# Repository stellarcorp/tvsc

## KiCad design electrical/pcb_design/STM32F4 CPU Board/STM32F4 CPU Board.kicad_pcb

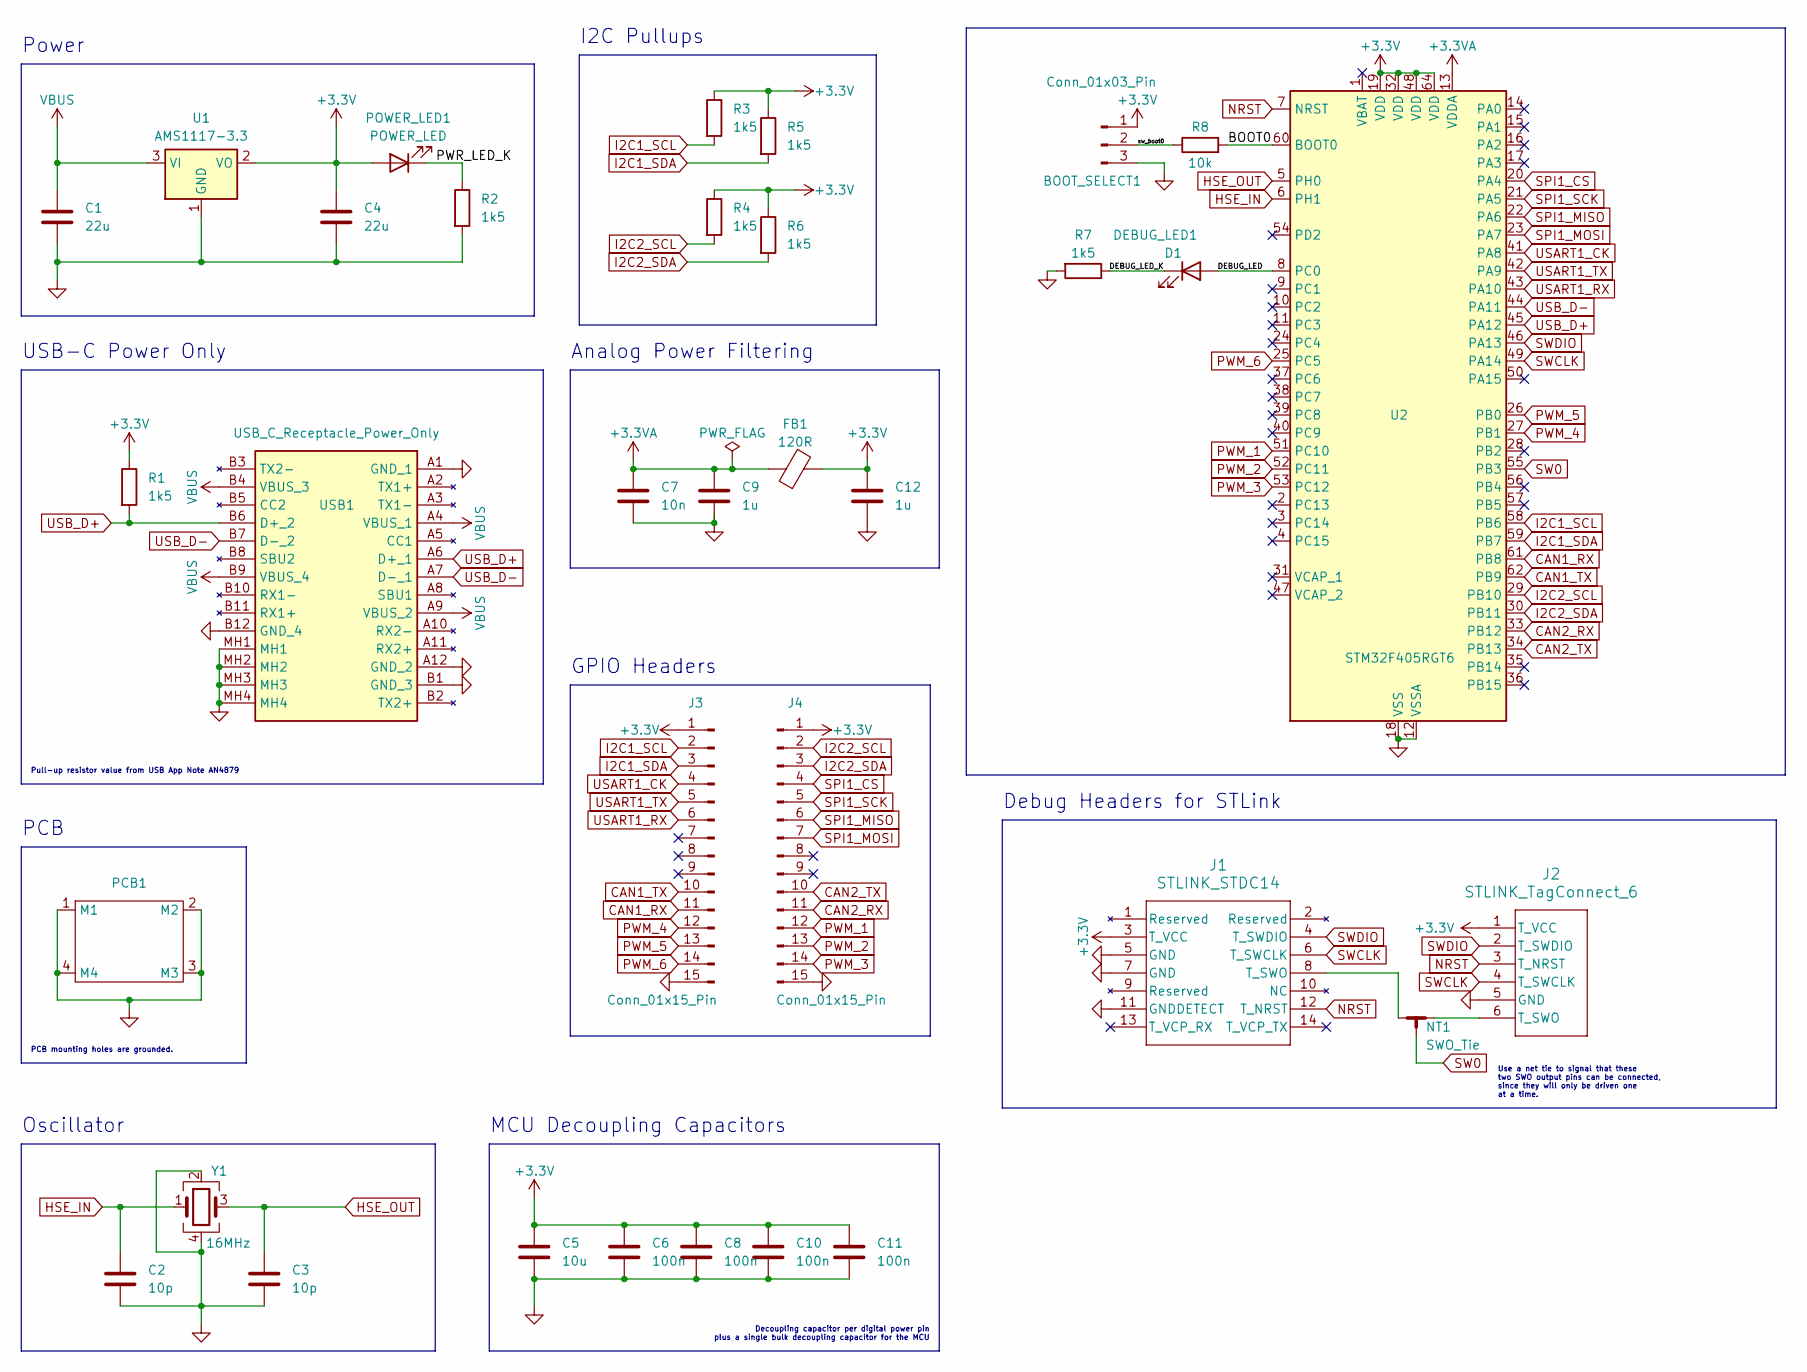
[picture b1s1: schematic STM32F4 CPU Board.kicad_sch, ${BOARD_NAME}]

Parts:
BOOT_SELECT1: Conn_01x03_Pin; PinHeader_1x03_P2.54mm_Vertical
C1, C4: 22u; C_0805_2012Metric; MPN C45783
C2, C3: 10p; C_0402_1005Metric; MPN C32949
C5: 10u; C_0603_1608Metric; MPN C19702
C6, C8, C10, C11: 100n; C_0402_1005Metric; MPN C1525
C7: 10n; C_0402_1005Metric; MPN C15195
C9, C12: 1u; C_0603_1608Metric; MPN C15849
D1: DEBUG_LED1; LED_0603_1608Metric; MPN C72041
FB1: 120R; L_0603_1608Metric; MPN C22787
J1: STLINK_STDC14; PinHeader_2x07_P1.27mm_Vertical; MPN C2881789
J2: STLINK_TagConnect_6; Tag-Connect_TC2030-IDC-NL_2x03_P1.27mm_Vertical
J3, J4: Conn_01x15_Pin; PinSocket_1x15_P2.54mm_Vertical; MPN C2883481
NT1: SWO_Tie; NetTie-3_SMD_Pad0.5mm
PCB1: Standard_PCB_Shape
POWER_LED1: POWER_LED; LED_0603_1608Metric; MPN C72043
R1, R2, R3, R4, R5, R6, R7: 1k5; R_0402_1005Metric; MPN C25867
R8: 10k; R_0402_1005Metric; MPN C25744
U1: AMS1117-3.3; SOT-223-3_TabPin2; MPN C6186
U2: STM32F405RGT6; LQFP-64_10x10mm_P0.5mm
USB1: USB_C_Receptacle_Power_Only; 12401832E402A; MPN C464604
Y1: 16MHz; Crystal_SMD_3225-4Pin_3.2x2.5mm; MPN C2857621

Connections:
+3.3V: BOOT_SELECT1.1, C4.1, C5.1, C6.1, C8.1, C10.1, C11.1, C12.1, FB1.2, J1.3 (T_VCC), J2.1 (T_VCC), J3.1, J4.1, POWER_LED1.2 (A), R1.1, R3.1, R4.1, R5.1, R6.1, U1.2 (VO), U2.19 (VDD), U2.32 (VDD), U2.48 (VDD), U2.64 (VDD)
+3.3VA: C7.1, C9.1, FB1.1, U2.13 (VDDA)
/BOOT0: R8.2, U2.60 (BOOT0)
/DEBUG_LED: D1.2 (A), U2.8 (PC0)
/DEBUG_LED_K: D1.1 (K), R7.1
/PWR_LED_K: POWER_LED1.1 (K), R2.1
/sw_boot0: BOOT_SELECT1.2, R8.1
CAN1_RX: J3.11, U2.61 (PB8)
CAN1_TX: J3.10, U2.62 (PB9)
CAN2_RX: J4.11, U2.33 (PB12)
CAN2_TX: J4.10, U2.34 (PB13)
GND: BOOT_SELECT1.3, C1.2, C2.2, C3.2, C4.2, C5.2, C6.2, C7.2, C8.2, C9.2, C10.2, C11.2, C12.2, J1.5 (GND), J1.7 (GND), J1.11 (GNDDETECT), J2.5 (GND), J3.15, J4.15, PCB1.1 (M1), PCB1.2 (M2), PCB1.3 (M3), PCB1.4 (M4), R2.2, R7.2, U1.1 (GND), U2.12 (VSSA), U2.18 (VSS), U2.63 (VSS), USB1.A1 (GND_1), USB1.A12 (GND_2), USB1.B1 (GND_3), USB1.B12 (GND_4), USB1.MH1, USB1.MH2, USB1.MH3, USB1.MH4, Y1.2, Y1.4
HSE_IN: C2.1, U2.6 (PH1), Y1.1
HSE_OUT: C3.1, U2.5 (PH0), Y1.3
I2C1_SCL: J3.2, R3.2, U2.58 (PB6)
I2C1_SDA: J3.3, R5.2, U2.59 (PB7)
I2C2_SCL: J4.2, R4.2, U2.29 (PB10)
I2C2_SDA: J4.3, R6.2, U2.30 (PB11)
NRST: J1.12 (T_NRST), J2.3 (T_NRST), U2.7 (NRST)
unnamed: J1.8 (T_SWO), NT1.1
unnamed: J2.6 (T_SWO), NT1.2
PWM_1: J4.12, U2.51 (PC10)
PWM_2: J4.13, U2.52 (PC11)
PWM_3: J4.14, U2.53 (PC12)
PWM_4: J3.12, U2.27 (PB1)
PWM_5: J3.13, U2.26 (PB0)
PWM_6: J3.14, U2.25 (PC5)
SPI1_CS: J4.4, U2.20 (PA4)
SPI1_MISO: J4.6, U2.22 (PA6)
SPI1_MOSI: J4.7, U2.23 (PA7)
SPI1_SCK: J4.5, U2.21 (PA5)
SW0: NT1.3, U2.55 (PB3)
SWCLK: J1.6 (T_SWCLK), J2.4 (T_SWCLK), U2.49 (PA14)
SWDIO: J1.4 (T_SWDIO), J2.2 (T_SWDIO), U2.46 (PA13)
USART1_CK: J3.4, U2.41 (PA8)
USART1_RX: J3.6, U2.43 (PA10)
USART1_TX: J3.5, U2.42 (PA9)
USB_D+: R1.2, U2.45 (PA12), USB1.A6 (D+_1), USB1.B6 (D+_2)
USB_D-: U2.44 (PA11), USB1.A7 (D-_1), USB1.B7 (D-_2)
VBUS: C1.1, U1.3 (VI), USB1.A4 (VBUS_1), USB1.A9 (VBUS_2), USB1.B4 (VBUS_3), USB1.B9 (VBUS_4)

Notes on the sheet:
Use a net tie to signal that these two SWO output pins can be connected, since they will only be driven one at a time.
GPIO Headers
Decoupling capacitor per digital power pin plus a single bulk decoupling capacitor for the MCU
I2C Pullups
PCB mounting holes are grounded.
PCB
Debug Headers for STLink
Power
Pull-up resistor value from USB App Note AN4879
MCU Decoupling Capacitors
Analog Power Filtering
Oscillator
USB-C Power Only

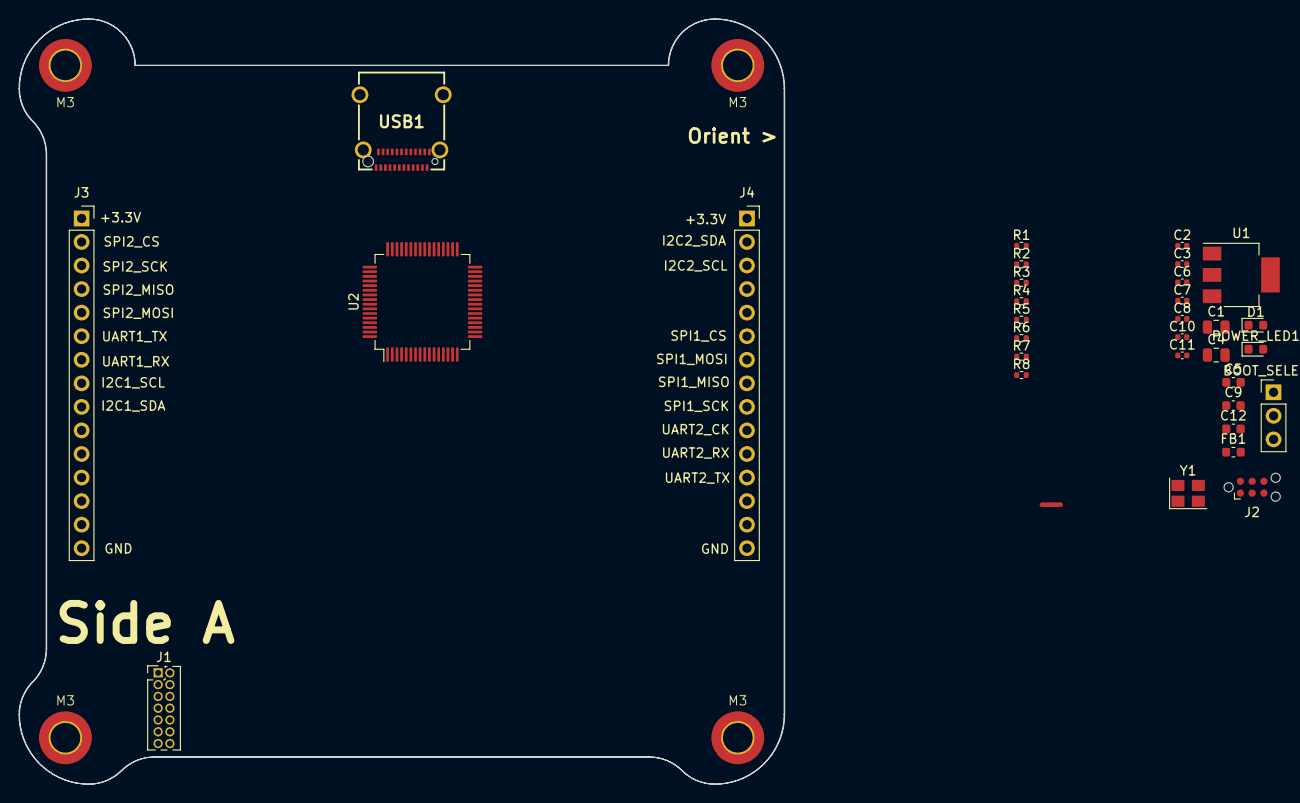
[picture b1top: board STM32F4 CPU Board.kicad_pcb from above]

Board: 2 copper layers, 82.5 x 82.5 mm, 34 parts (0 on the bottom side), 40 nets.

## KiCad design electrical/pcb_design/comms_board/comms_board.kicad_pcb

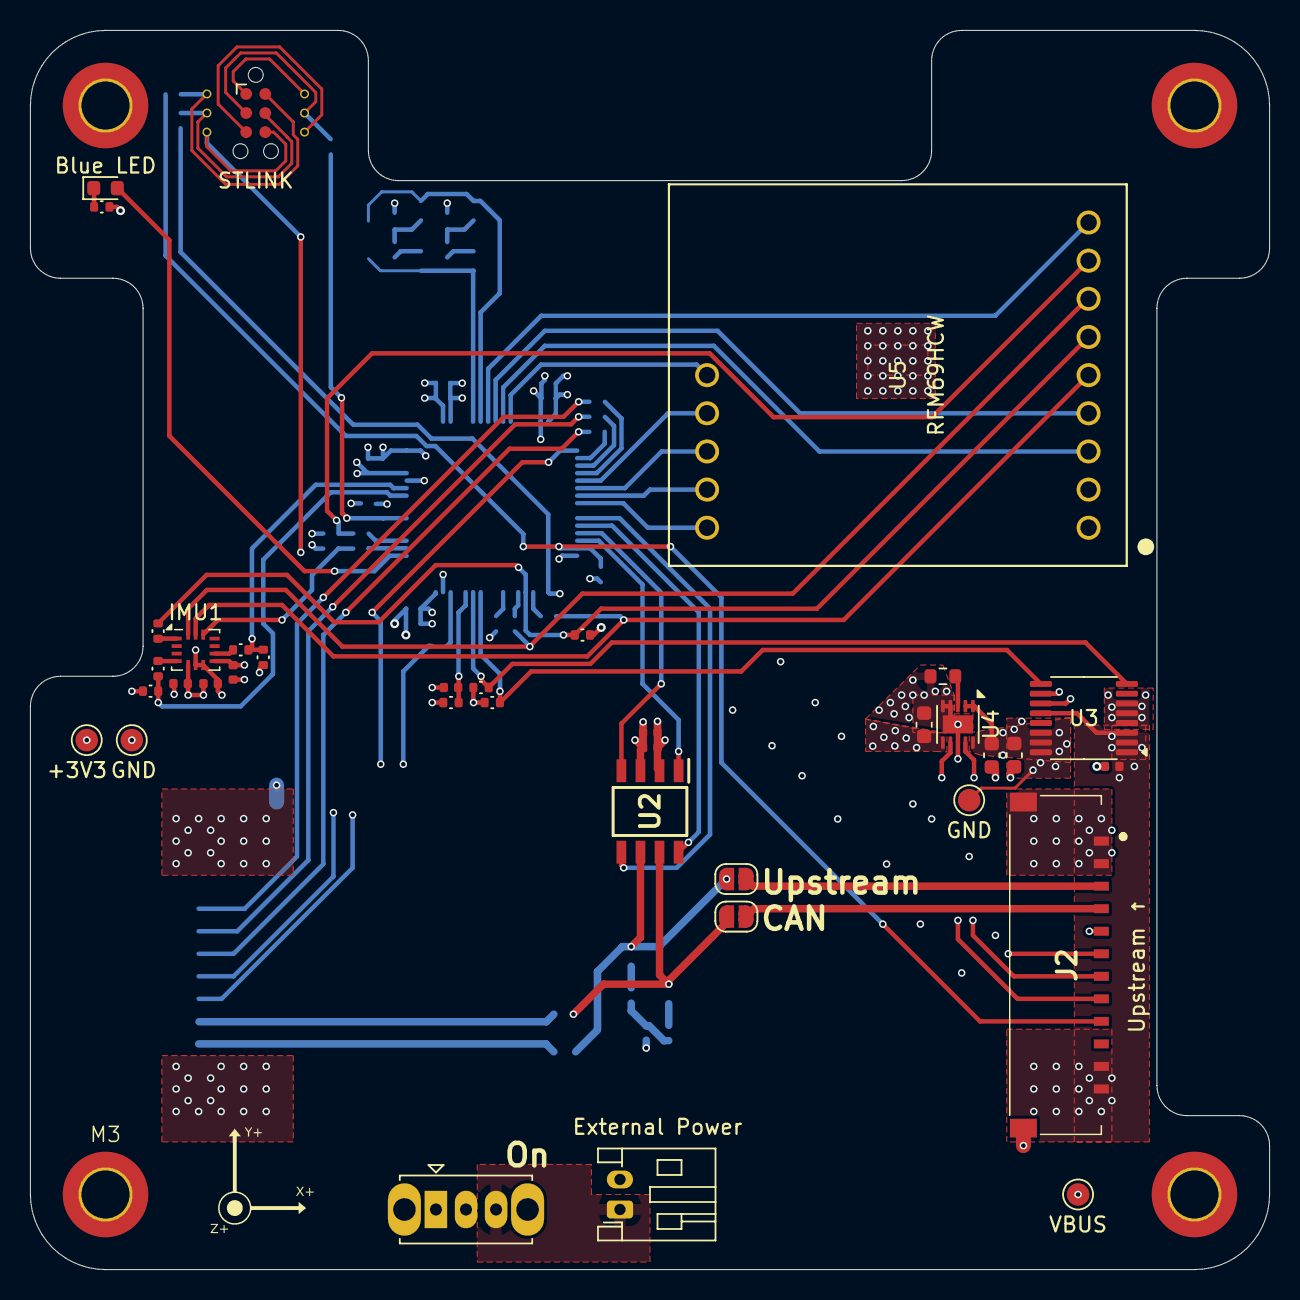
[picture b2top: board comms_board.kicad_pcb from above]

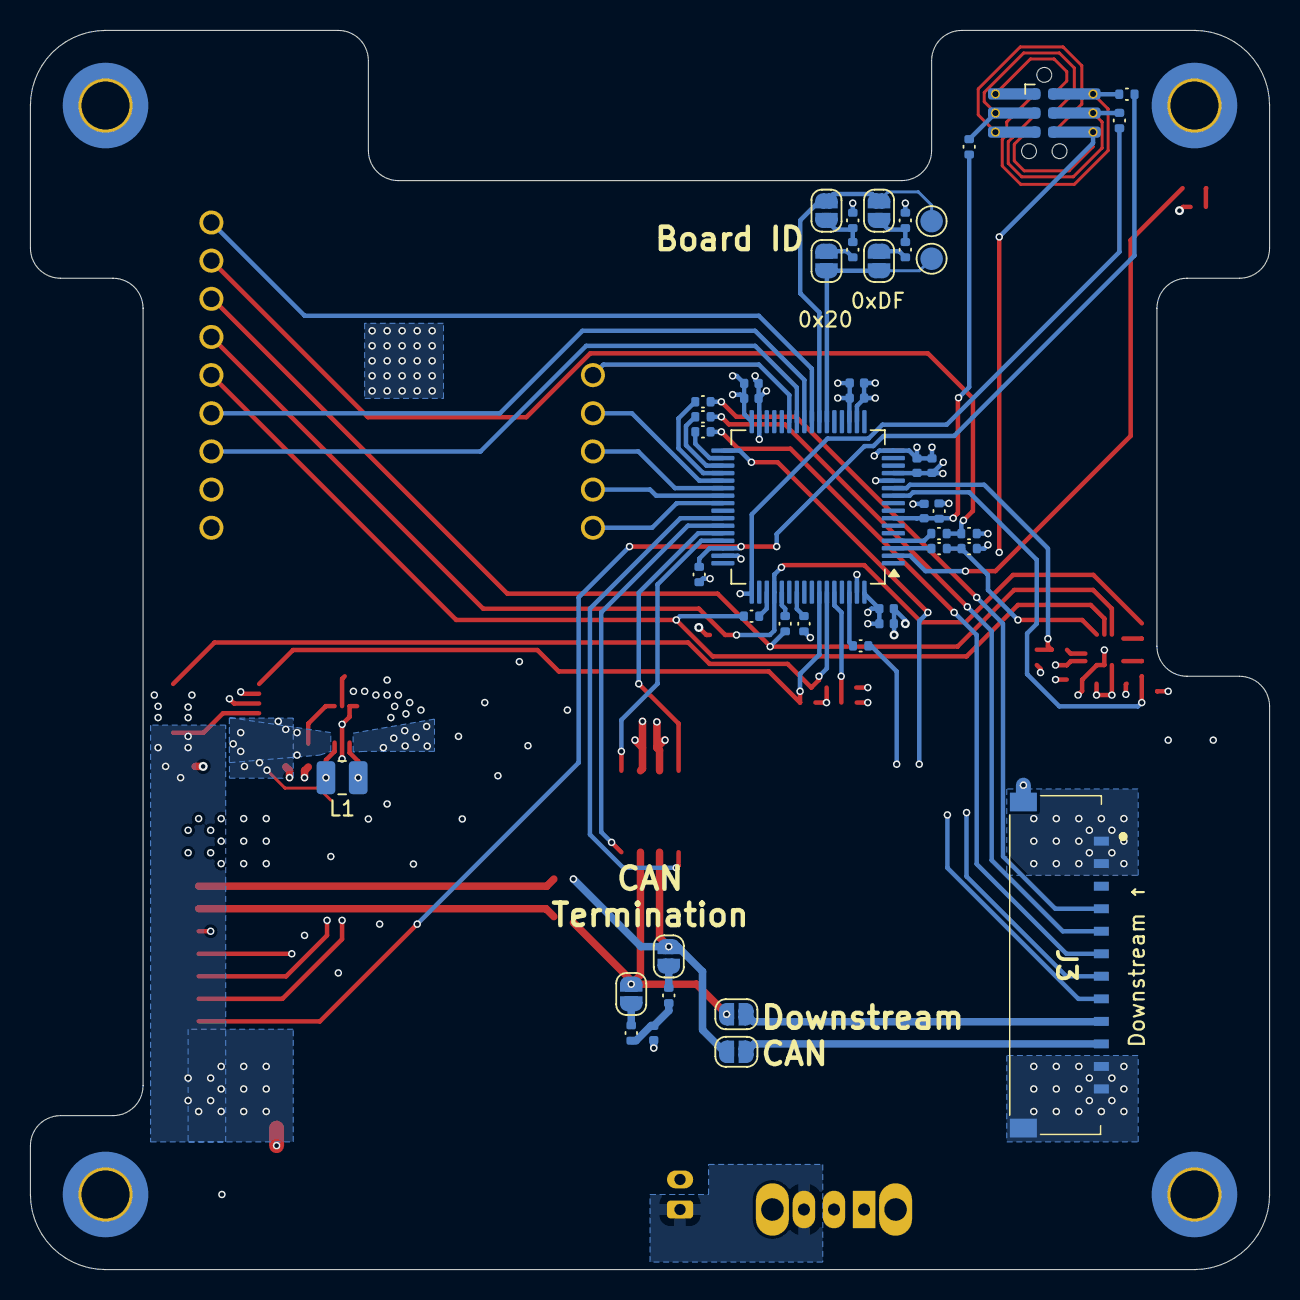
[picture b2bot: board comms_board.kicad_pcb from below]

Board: 4 copper layers, 82.5 x 82.5 mm, 83 parts (46 on the bottom side), 71 nets.

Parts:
C1, C2, C3, C7, C8, C9, C13, C14, C19, C20: 100n; Nondescript_C_0402_1005Metric
C4: 10u; Nondescript_C_0402_1005Metric
C5, C17: 22u; Nondescript_C_0603_1608Metric
C6: 10u; Nondescript_C_0603_1608Metric
C10, C11, C12, C15, C16, C18: 1u; Nondescript_C_0402_1005Metric
D1: Blue LED; LED_0603_1608Metric
J1: STLINK; Double-Sided_Tag-Connect_TC2030-IDC-NL_2x03_P1.27mm_Vertical
J2: Molex_504050-1291; Bus Connector (Target)
J3: Molex_504050-1291; Bus Connector (Control)
J4: External Power; JST_PH_S2B-PH-K_1x02_P2.00mm_Horizontal
JP1, JP2, JP3, JP4, JP5, JP6: SolderJumper_2_Open; SolderJumper-2_P1.3mm_Open_RoundedPad1.0x1.5mm
JP7, JP9: 0xDF; SolderJumper-2_P1.3mm_Open_RoundedPad1.0x1.5mm
JP8, JP10: 0x20; SolderJumper-2_P1.3mm_Open_RoundedPad1.0x1.5mm
L1: 2.2µH; L_1008_2520Metric
PCB1: Core_Board_Shape_Space_Invader_2
R1, R3, R6, R11, R12, R17, R25, R26, R33, R48: 9k31; Nondescript_R_0402_1005Metric
R2, R4, R5, R7, R8, R9, R18, R19, R20, R21, R22, R23, R34, R37, R38, R39: 33; Nondescript_R_0402_1005Metric
R10: 36k5; Nondescript_R_0603_1608Metric
R13, R16: 3k16; Nondescript_R_0402_1005Metric
R14, R15: 221k; Nondescript_R_0402_1005Metric
R49, R50: 60; Nondescript_R_0402_1005Metric
SW1: SW_SPDT; SW_Slide_SPDT_Straight_CK_OS102011MS2Q
TP1: VBUS; TestPoint_Pad_D1.5mm
TP2, TP3: GND; TestPoint_Pad_D1.5mm
TP4: +3V3; TestPoint_Pad_D1.5mm
TP5: BOARD_ID_SENSE; TestPoint_Pad_D1.5mm
TP6: BOARD_ID_POWER; TestPoint_Pad_D1.5mm
U1: STM32L452RCTx; LQFP-64_10x10mm_P0.5mm
U2: TCAN330DR; SOIC127P600X175-8N
U3: INA260; TSSOP-16_4.4x5mm_P0.65mm
U4: TPS63900; WSON-10-1EP_2.5x2.5mm_P0.5mm_EP1.2x2mm
U5: RFM69HCW; RFM69HCW_Adafruit_Breakout
U6: IMU1; Bosch_LGA-14_3x2.5mm_P0.5mm

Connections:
+3V3: C5.1, C7.1, C8.1, C9.1, C10.1, C11.1, C12.1, C13.1, C14.1, C15.1, C16.1, C18.1, C19.1, C20.1, J1.1 (T_VCC), R1.1, R6.1, R11.1, R12.1, R17.1, R25.1, R26.1, R33.1, R48.1, TP4.1, U1.13 (VDDA), U1.19 (VDD), U1.32 (VDD), U1.64 (VDD), U2.3 (VCC), U3.10 (VS), U4.6 (VOUT), U5.1 (VIN), U6.5 (VDDIO), U6.8 (VDD)
/BOOT0: C2.1, J2.5 (BOOT0), R3.1, U1.60 (PH3)
/Board Identification/BOARD_ID_POWER: JP9.1 (A), JP10.1 (A), TP6.1, U1.22 (PA6)
/Board Identification/BOARD_ID_SENSE: JP7.1 (A), JP8.1 (A), TP5.1, U1.23 (PA7)
/CAN bus/CANH_TERMINATION: JP3.2 (B), R49.1
/CAN bus/CANL_TERMINATION: JP4.1 (A), R50.2
/CAN bus/CAN_RX: U1.44 (PA11), U2.4 (RXD)
/CAN bus/CAN_SHUTDOWN: U1.42 (PA9), U2.5 (SHDN)
/CAN bus/CAN_SILENT: U1.43 (PA10), U2.8 (S)
/CAN bus/CAN_TX: U1.45 (PA12), U2.1 (TXD)
/CANH_DOWNSTREAM: J3.9 (CANH), JP5.2 (B)
/CANH_UPSTREAM: J2.4 (CANH), JP1.1 (A)
/CANL_DOWNSTREAM: J3.10 (CANL), JP6.2 (B)
/CANL_UPSTREAM: J2.3 (CANL), JP2.1 (A)
/CTRL.BOOT0: J3.8 (BOOT0_CTRL), R7.2
/CTRL.NRST: J3.5 (NRST_CTRL), R5.2
/CTRL.SWCLK: J3.6 (SWCLK_CTRL), R8.2
/CTRL.SWDIO: J3.4 (SWDIO_CTRL), R9.2
/CTRL.SWO: J3.7 (SWO_CTRL), U1.33 (PB12)
/IMU/IMU1_INT1: R22.2, R26.2, U1.10 (PC2)
/IMU/IMU1_INT2: R23.2, R25.2, U1.11 (PC3)
/IMU/IMU1_SPI_CS: R33.2, R34.1, U6.12 (CSB)
/MCU/DEBUG_LED: D1.2 (A), U1.2 (PC13)
/MCU/I2C1_SCL: R12.2, U1.58 (PB6), U3.9 (SCL)
/MCU/I2C1_SDA: R11.2, U1.59 (PB7), U3.8 (SDA)
/MCU/TRANSCEIVER_EN: U1.26 (PB0), U5.3 (EN)
/MCU/TRANSCEIVER_INT0: U1.25 (PC5), U5.4 (G0)
/MCU/TRANSCEIVER_INT1: U1.40 (PC9), U5.14 (G1)
/MCU/TRANSCEIVER_INT2: U1.39 (PC8), U5.13 (G2)
/MCU/TRANSCEIVER_INT3: U1.38 (PC7), U5.12 (G3)
/MCU/TRANSCEIVER_INT4: U1.37 (PC6), U5.11 (G4)
/MCU/TRANSCEIVER_INT5: U1.27 (PB1), U5.10 (G5)
/MCU/TRANSCEIVER_RESET: U1.24 (PC4), U5.9 (RST)
/MCU/TRANSCEIVER_SPI_CS: R21.1, R48.2, U5.8 (CS)
/NRST: C1.1, J2.8 (NRST), R1.2, R37.1, U1.7 (NRST)
/Power Monitoring and Voltage Regulation/EXT_POWER+: J4.1, SW1.3 (C)
/SPI3.MISO: R17.2, R20.1, U1.52 (PC11), U5.6 (MISO)
/SPI3.MOSI: R19.1, U5.7 (MOSI), U6.14 (SDx)
/SPI3.SCK: R18.1, U5.5 (SCK), U6.13 (SCx)
/SWCLK: J2.7 (SWCLK), R39.1, U1.49 (PA14)
/SWDIO: J2.9 (SWDIO), R6.2, R38.1, U1.46 (PA13)
/SWO: J1.6 (T_SWO), J2.6 (SWO), R4.2
GND: C1.2, C2.2, C3.1, C4.2, C5.2, C6.2, C7.2, C8.2, C9.2, C10.2, C11.2, C12.2, C13.2, C14.2, C15.2, C16.2, C17.2, C18.2, C19.2, C20.2, J1.5 (GND), J2.1 (GND), J2.2 (GND), J2.MP1, J2.MP2, J3.11 (GND), J3.12 (GND), J3.MP1, J3.MP2, J4.2, PCB1.MH1, PCB1.MH2, PCB1.MH3, PCB1.MH4, R2.2, R3.2, R10.2, R14.2, R16.2, TP3.1, U1.12 (VSSA), U1.16 (PA2), U1.18 (VSS), U1.31 (VSS), U1.47 (VSS), U1.63 (VSS), U2.2 (GND), U3.4 (A1), U3.5 (A0), U3.6 (GND), U3.11 (GND), U4.4 (CFG2), U4.5 (CFG3), U4.8 (GND), U4.11 (GND), U5.2 (GND), U6.6 (GNDIO), U6.7 (GND)
unnamed: C3.2, R49.2, R50.1
unnamed: D1.1 (K), R2.1
unnamed: J1.3 (T_NRST), R37.2
unnamed: J1.4 (T_SWCLK), R39.2
unnamed: J1.2 (T_SWDIO), R38.2
unnamed: JP1.2 (B), JP3.1 (A), JP5.1 (A), U2.7 (CANH)
unnamed: JP2.2 (B), JP4.2 (B), JP6.1 (A), U2.6 (CANL)
unnamed: JP7.2 (B), R13.2, R14.1
unnamed: JP8.2 (B), R15.2, R16.1
unnamed: JP9.2 (B), R13.1
unnamed: JP10.2 (B), R15.1
unnamed: R4.1, U1.55 (PB3)
unnamed: R7.1, U1.62 (PB9)
unnamed: R8.1, U1.34 (PB13)
unnamed: R5.1, U1.35 (PB14)
unnamed: R9.1, U1.36 (PB15)
unnamed: R18.2, U1.51 (PC10)
unnamed: R19.2, U1.53 (PC12)
unnamed: R34.2, U1.3 (PC14)
unnamed: R21.2, U1.4 (PC15)
unnamed: R10.1, U4.3 (CFG1)
unnamed: L1.2, U4.9 (LX1)
unnamed: L1.1, U4.7 (LX2)
unnamed: R22.1, U6.4 (INT1)
unnamed: R23.1, U6.9 (INT2)
unnamed: R20.2, U6.1 (SDO)
VBUS: C4.1, J2.11 (VBUS), J2.12 (VBUS), J3.1 (VBUS), J3.2 (VBUS), SW1.2 (B), TP1.1, U3.1 (IN+), U3.2 (IN+), U3.3 (IN+), U3.12 (VBUS)
VCC: C6.1, C17.1, TP2.1, U3.14 (IN-), U3.15 (IN-), U3.16 (IN-), U4.1 (EN), U4.2 (SEL), U4.10 (VIN)

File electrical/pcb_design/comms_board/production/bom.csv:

Designator,Footprint,Quantity,Value,LCSC Part #
"C1, C13, C14, C19, C2, C20, C3, C7, C8, C9",Nondescript_C_0402_1005Metric,10,100n,C1525
"C10, C11, C12, C15, C16, C18",Nondescript_C_0402_1005Metric,6,1u,C52923
"C17, C5",Nondescript_C_0603_1608Metric,2,22u,C710887
C4,Nondescript_C_0402_1005Metric,1,10u,C15525
C6,Nondescript_C_0603_1608Metric,1,10u,C77041
D1,0603,1,Blue LED,C72041
J2,Bus Connector (Target),1,Molex_504050-1291,C563982
J3,Bus Connector (Control),1,Molex_504050-1291,C563982
L1,1008,1,2.2µH,C576403
"R1, R11, R12, R17, R25, R26, R3, R33, R48, R6",Nondescript_R_0402_1005Metric,10,9k31,C270572
R10,Nondescript_R_0603_1608Metric,1,36k5,C23029
"R13, R16",Nondescript_R_0402_1005Metric,2,3k16,C11462
"R14, R15",Nondescript_R_0402_1005Metric,2,221k,C26998
"R18, R19, R2, R20, R21, R22, R23, R34, R37, R38, R39, R4, R5, R7, R8, R9",Nondescript_R_0402_1005Metric,16,33,C25105
"R49, R50",Nondescript_R_0402_1005Metric,2,60,C60310
U1,LQFP-64_10x10mm_P0.5mm,1,STM32L452RCTx,C192722
U2,SOIC127P600X175-8N,1,TCAN330DR,C2652876
U3,TSSOP-16_4.4x5mm_P0.65mm,1,INA260,C2155885
U4,WSON-10-1EP_2.5x2.5mm_P0.5mm_EP1.2x2mm,1,TPS63900,C1518762
U6,Bosch_LGA-14_3x2.5mm_P0.5mm,1,IMU1,C5368700

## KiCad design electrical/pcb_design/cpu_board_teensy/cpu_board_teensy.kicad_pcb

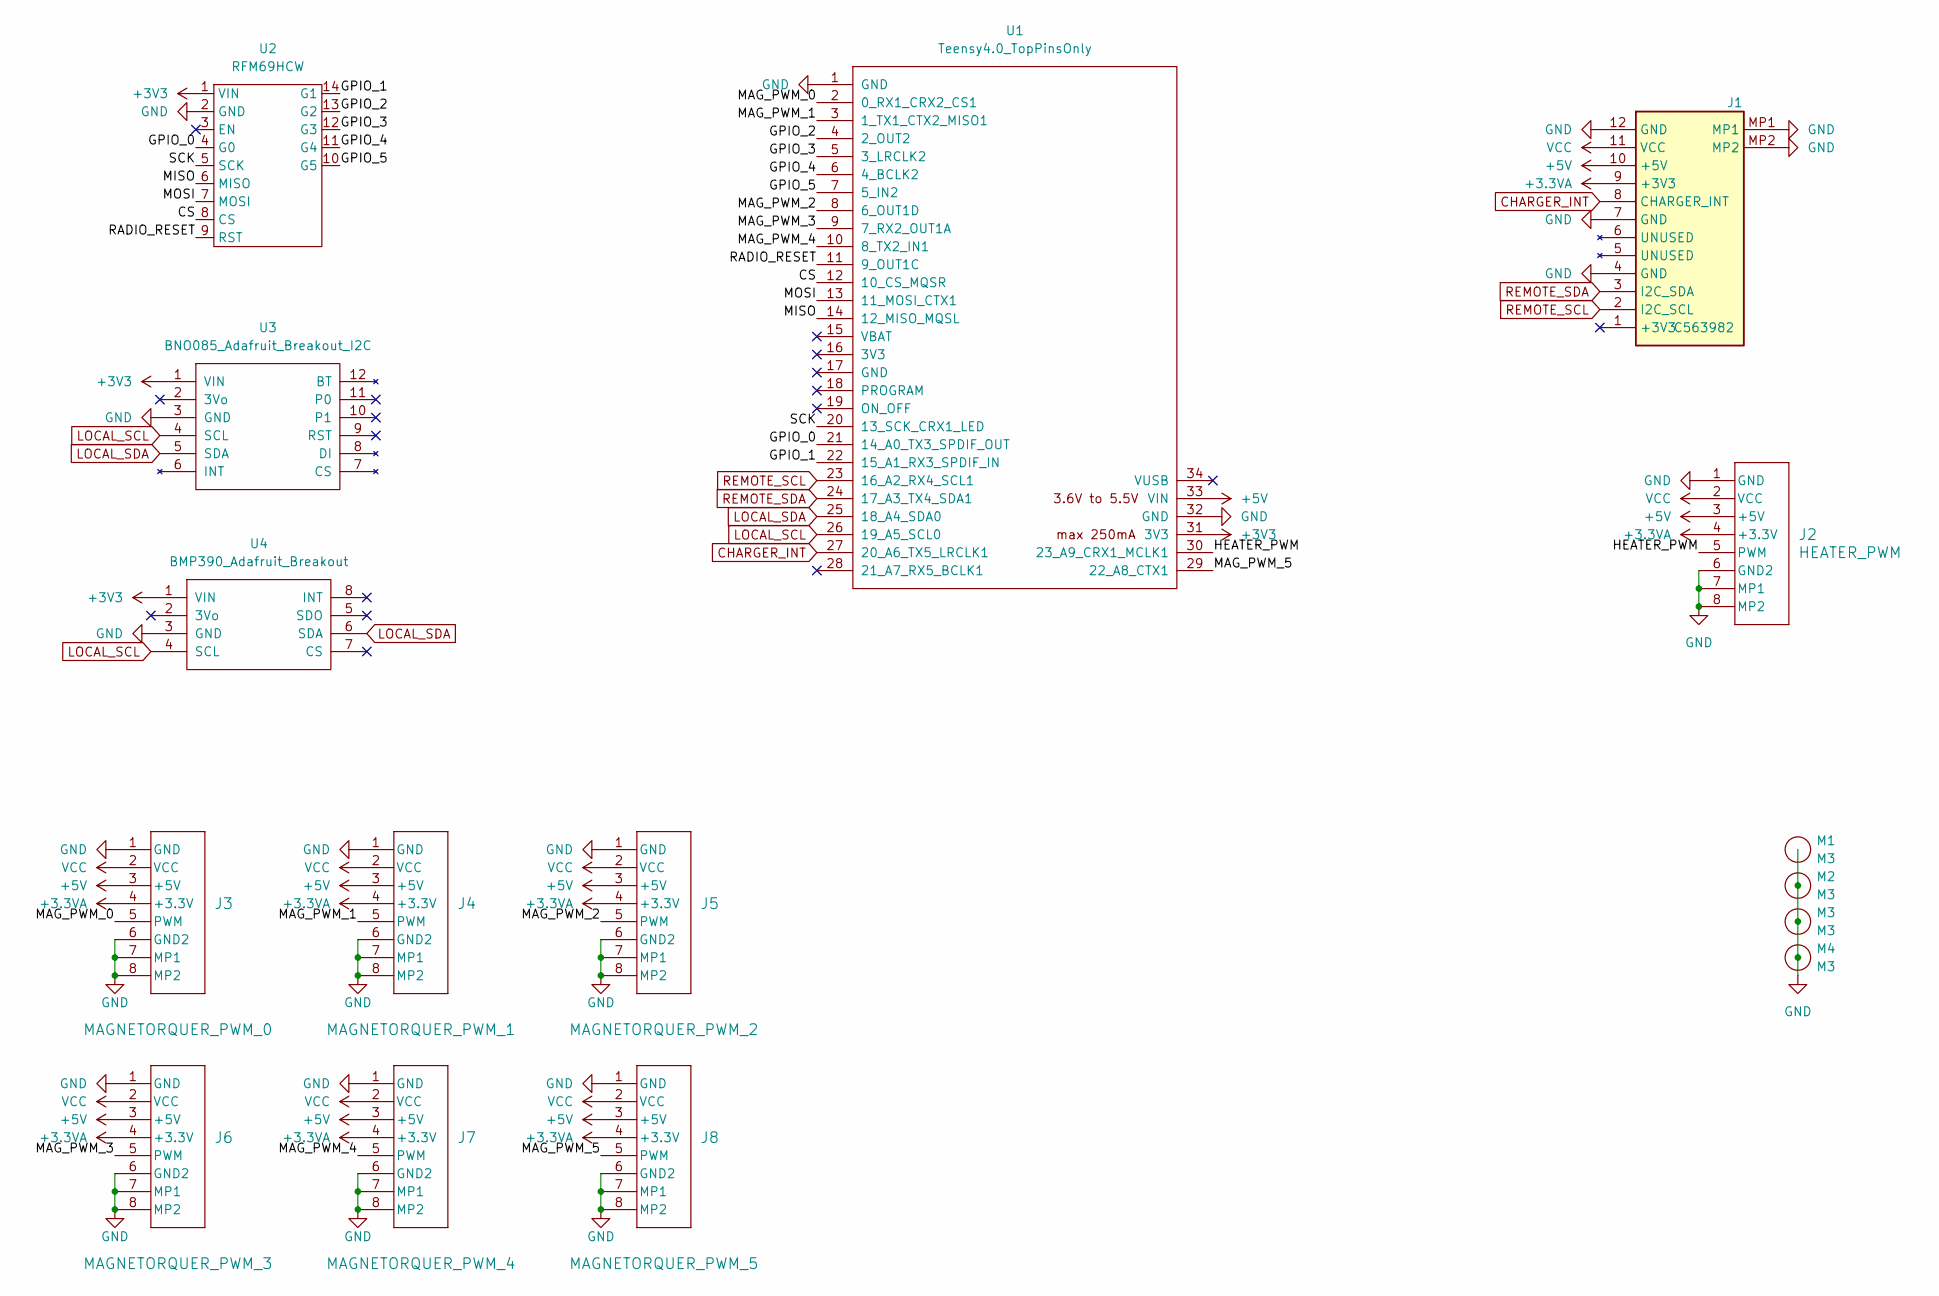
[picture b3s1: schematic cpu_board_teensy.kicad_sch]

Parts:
J1: Interconnect_Power_CPU-Power_side; 5040501291; MPN C563982
J2: HEATER_PWM; Molex_5013310607; MPN C587861
J3: MAGNETORQUER_PWM_0; Molex_5013310607; MPN C587861
J4: MAGNETORQUER_PWM_1; Molex_5013310607; MPN C587861
J5: MAGNETORQUER_PWM_2; Molex_5013310607; MPN C587861
J6: MAGNETORQUER_PWM_3; Molex_5013310607; MPN C587861
J7: MAGNETORQUER_PWM_4; Molex_5013310607; MPN C587861
J8: MAGNETORQUER_PWM_5; Molex_5013310607; MPN C587861
M1, M2, M3, M4: M3; MountingHole_3.2mm_M3_ISO7380_Pad_TopBottom
U1: Teensy4.0_TopPinsOnly; Teensy40_TopPinsOnly
U2: RFM69HCW; RFM69HCW_Adafruit_Breakout
U3: BNO085_Adafruit_Breakout_I2C; BNO085_Adafruit_Breakout
U4: BMP390_Adafruit_Breakout

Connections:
+3.3VA: J1.9 (+3V3), J2.4 (+3.3V), J3.4 (+3.3V), J4.4 (+3.3V), J5.4 (+3.3V), J6.4 (+3.3V), J7.4 (+3.3V), J8.4 (+3.3V)
+3V3: U1.31 (3V3), U2.1 (VIN), U3.1 (VIN), U4.1 (VIN)
+5V: J1.10 (+5V), J2.3 (+5V), J3.3 (+5V), J4.3 (+5V), J5.3 (+5V), J6.3 (+5V), J7.3 (+5V), J8.3 (+5V), U1.33 (VIN)
/CS: U1.12 (10_CS_MQSR), U2.8 (CS)
/GPIO_0: U1.21 (14_A0_TX3_SPDIF_OUT), U2.4 (G0)
/GPIO_1: U1.22 (15_A1_RX3_SPDIF_IN), U2.14 (G1)
/GPIO_2: U1.4 (2_OUT2), U2.13 (G2)
/GPIO_3: U1.5 (3_LRCLK2), U2.12 (G3)
/GPIO_4: U1.6 (4_BCLK2), U2.11 (G4)
/GPIO_5: U1.7 (5_IN2), U2.10 (G5)
/HEATER_PWM: J2.5 (PWM), U1.30 (23_A9_CRX1_MCLK1)
/MAG_PWM_0: J3.5 (PWM), U1.2 (0_RX1_CRX2_CS1)
/MAG_PWM_1: J4.5 (PWM), U1.3 (1_TX1_CTX2_MISO1)
/MAG_PWM_2: J5.5 (PWM), U1.8 (6_OUT1D)
/MAG_PWM_3: J6.5 (PWM), U1.9 (7_RX2_OUT1A)
/MAG_PWM_4: J7.5 (PWM), U1.10 (8_TX2_IN1)
/MAG_PWM_5: J8.5 (PWM), U1.29 (22_A8_CTX1)
/MISO: U1.14 (12_MISO_MQSL), U2.6 (MISO)
/MOSI: U1.13 (11_MOSI_CTX1), U2.7 (MOSI)
/RADIO_RESET: U1.11 (9_OUT1C), U2.9 (RST)
/SCK: U1.20 (13_SCK_CRX1_LED), U2.5 (SCK)
CHARGER_INT: J1.8 (CHARGER_INT), U1.27 (20_A6_TX5_LRCLK1)
GND: J1.4 (GND), J1.7 (GND), J1.12 (GND), J1.MP1, J1.MP2, J2.1 (GND), J2.6 (GND2), J2.7 (MP1), J2.8 (MP2), J3.1 (GND), J3.6 (GND2), J3.7 (MP1), J3.8 (MP2), J4.1 (GND), J4.6 (GND2), J4.7 (MP1), J4.8 (MP2), J5.1 (GND), J5.6 (GND2), J5.7 (MP1), J5.8 (MP2), J6.1 (GND), J6.6 (GND2), J6.7 (MP1), J6.8 (MP2), J7.1 (GND), J7.6 (GND2), J7.7 (MP1), J7.8 (MP2), J8.1 (GND), J8.6 (GND2), J8.7 (MP1), J8.8 (MP2), M1.1 (Hole), M2.1 (Hole), M3.1 (Hole), M4.1 (Hole), U1.1 (GND), U1.32 (GND), U2.2 (GND), U3.3 (GND), U4.3 (GND)
LOCAL_SCL: U1.26 (19_A5_SCL0), U3.4 (SCL), U4.4 (SCL)
LOCAL_SDA: U1.25 (18_A4_SDA0), U3.5 (SDA), U4.6 (SDA)
REMOTE_SCL: J1.2 (I2C_SCL), U1.23 (16_A2_RX4_SCL1)
REMOTE_SDA: J1.3 (I2C_SDA), U1.24 (17_A3_TX4_SDA1)
VCC: J1.11 (VCC), J2.2 (VCC), J3.2 (VCC), J4.2 (VCC), J5.2 (VCC), J6.2 (VCC), J7.2 (VCC), J8.2 (VCC)

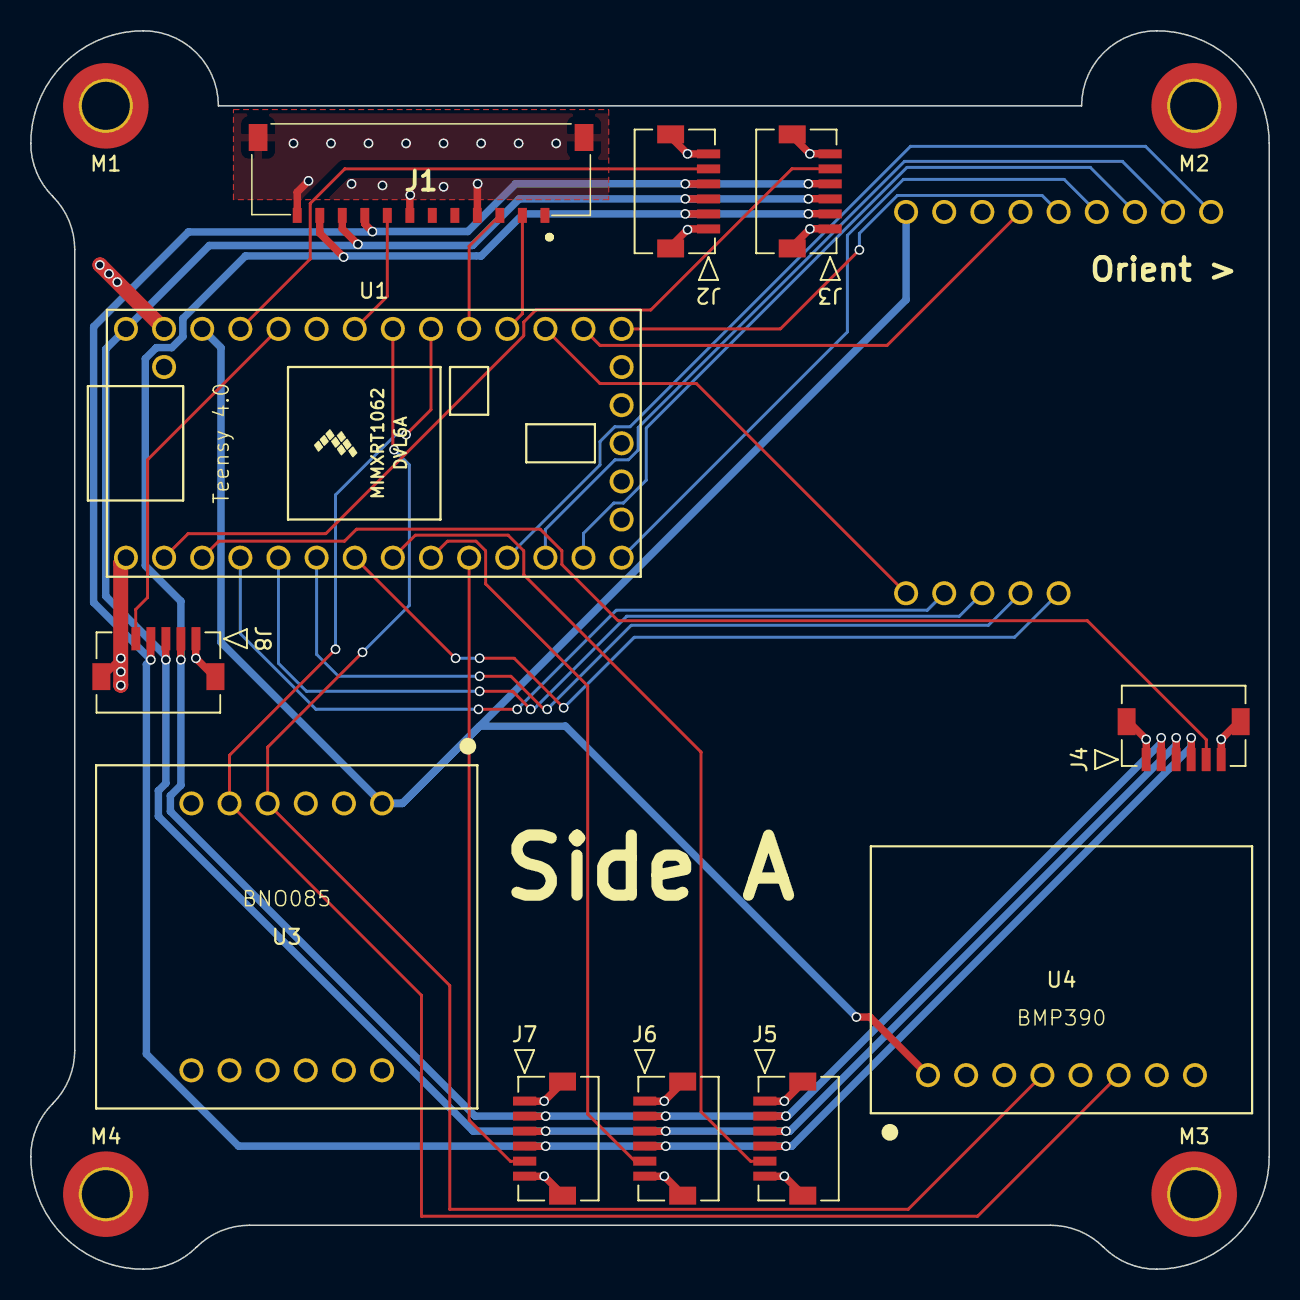
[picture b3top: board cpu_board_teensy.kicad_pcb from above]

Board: 2 copper layers, 82.5 x 82.5 mm, 16 parts (1 on the bottom side), 28 nets.

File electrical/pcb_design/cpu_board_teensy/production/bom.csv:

Designator,Footprint,Quantity,Value,LCSC Part #
J1,5040501291,1,Molex_504050-1291,C563982
J2,Molex_5013310607,1,HEATER_PWM,C587861
J3,Molex_5013310607,1,MAGNETORQUER_PWM_0,C587861
J4,Molex_5013310607,1,MAGNETORQUER_PWM_1,C587861
J5,Molex_5013310607,1,MAGNETORQUER_PWM_2,C587861
J6,Molex_5013310607,1,MAGNETORQUER_PWM_3,C587861
J7,Molex_5013310607,1,MAGNETORQUER_PWM_4,C587861
J8,Molex_5013310607,1,MAGNETORQUER_PWM_5,C587861
U1,Teensy40_TopPinsOnly,1,Teensy4.0_TopPinsOnly,
U2,RFM69HCW_Adafruit_Breakout,1,RFM69HCW,
U3,BNO085_Adafruit_Breakout,1,BNO085_Adafruit_Breakout_I2C,
U4,BMP390_Adafruit_Breakout,1,BMP390,

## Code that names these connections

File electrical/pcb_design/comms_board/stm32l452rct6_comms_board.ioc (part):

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Mcu.Name=STM32L452R(C-E)Tx
Mcu.Package=LQFP64
Mcu.UserName=STM32L452RCTx
PA10.GPIOParameters=GPIO_Label
PA10.GPIO_Label=CAN1_SILENT
PA10.Signal=GPIO_Output
PA11.Mode=CAN_Activate
PA11.Signal=CAN1_RX
PA12.Mode=CAN_Activate
PA12.Signal=CAN1_TX
PA13\ (JTMS/SWDIO).Mode=Serial_Wire
PA13\ (JTMS/SWDIO).Signal=SYS_JTMS-SWDIO
PA14\ (JTCK/SWCLK).Mode=Serial_Wire
PA14\ (JTCK/SWCLK).Signal=SYS_JTCK-SWCLK
PA6.GPIOParameters=GPIO_Label
PA6.GPIO_Label=BOARD_ID_POWER
PA6.Signal=GPIO_Output
PA7.GPIOParameters=GPIO_Label
PA7.GPIO_Label=BOARD_ID_SENSE
PA7.Signal=ADCx_IN12
PA9.GPIOParameters=GPIO_Label
PA9.GPIO_Label=CAN1_SHUTDOWN
PA9.Signal=GPIO_Output
PB10.Mode=I2C
PB10.Signal=I2C2_SCL
PB11.Mode=I2C
PB11.Signal=I2C2_SDA
PB12.GPIOParameters=GPIO_Label
PB12.GPIO_Label=SWO_CONTROL
PB12.Signal=GPIO_Output
PB13.GPIOParameters=GPIO_Label
PB13.GPIO_Label=SWCLK_CONTROL
PB13.Signal=GPIO_Output
PB14.GPIOParameters=GPIO_Label
PB14.GPIO_Label=NRST_CONTROL
PB14.Signal=GPIO_Output
PB15.GPIOParameters=GPIO_Label
PB15.GPIO_Label=SWDIO_CONTROL
PB15.Signal=GPIO_Output
PB3\ (JTDO/TRACESWO).Signal=SYS_JTDO-SWO
PB6.Mode=I2C
PB6.Signal=I2C1_SCL
PB7.Mode=I2C
PB7.Signal=I2C1_SDA
PB8.GPIOParameters=GPIO_PuPd,GPIO_Label
PB8.GPIO_Label=NMAG_FAULT
PB8.GPIO_PuPd=GPIO_PULLUP
PB8.Signal=GPIO_Input
PB9.GPIOParameters=GPIO_Label
PB9.GPIO_Label=BOOT0_CONTROL
PB9.Signal=GPIO_Output
PC0.Mode=I2C
PC0.Signal=I2C3_SCL
PC1.Mode=I2C
PC1.Signal=I2C3_SDA
PC10.Mode=Full_Duplex_Master
PC10.Signal=SPI3_SCK
PC11.Mode=Full_Duplex_Master
PC11.Signal=SPI3_MISO
PC12.Mode=Full_Duplex_Master
PC12.Signal=SPI3_MOSI
PC13.GPIOParameters=GPIO_Label
PC13.GPIO_Label=DEBUG_LED
PC13.Signal=GPIO_Output
PC14-OSC32_IN\ (PC14).GPIOParameters=GPIO_Label
PC14-OSC32_IN\ (PC14).GPIO_Label=IMU1_SPI_CS
PC14-OSC32_IN\ (PC14).Signal=GPIO_Output
PC15-OSC32_OUT\ (PC15).GPIOParameters=GPIO_Label
PC15-OSC32_OUT\ (PC15).GPIO_Label=IMU_MAG_INT1
PC15-OSC32_OUT\ (PC15).Signal=GPIO_Input
PC2.GPIOParameters=GPIO_Label
PC2.GPIO_Label=IMU1_INT1
PC2.Signal=GPXTI2
PC3.GPIOParameters=GPIO_Label
PC3.GPIO_Label=IMU1_INT2
PC3.Signal=GPXTI3
PC6.GPIOParameters=GPIO_Label
PC6.GPIO_Label=IMU2_INT2
PC6.Signal=GPXTI6
PC7.GPIOParameters=GPIO_Label
PC7.GPIO_Label=IMU2_INT1
PC7.Signal=GPXTI7
PC8.GPIOParameters=GPIO_Label
PC8.GPIO_Label=IMU_MAG_SPI_CS
PC8.Signal=GPIO_Output
PC9.GPIOParameters=GPIO_Label
PC9.GPIO_Label=IMU2_SPI_CS
PC9.Signal=GPIO_Output
RCC.HSE_VALUE=8000000
RCC.SYSCLKFreq_VALUE=16000000
RCC.SYSCLKSource=RCC_SYSCLKSOURCE_PLLCLK
board=custom
